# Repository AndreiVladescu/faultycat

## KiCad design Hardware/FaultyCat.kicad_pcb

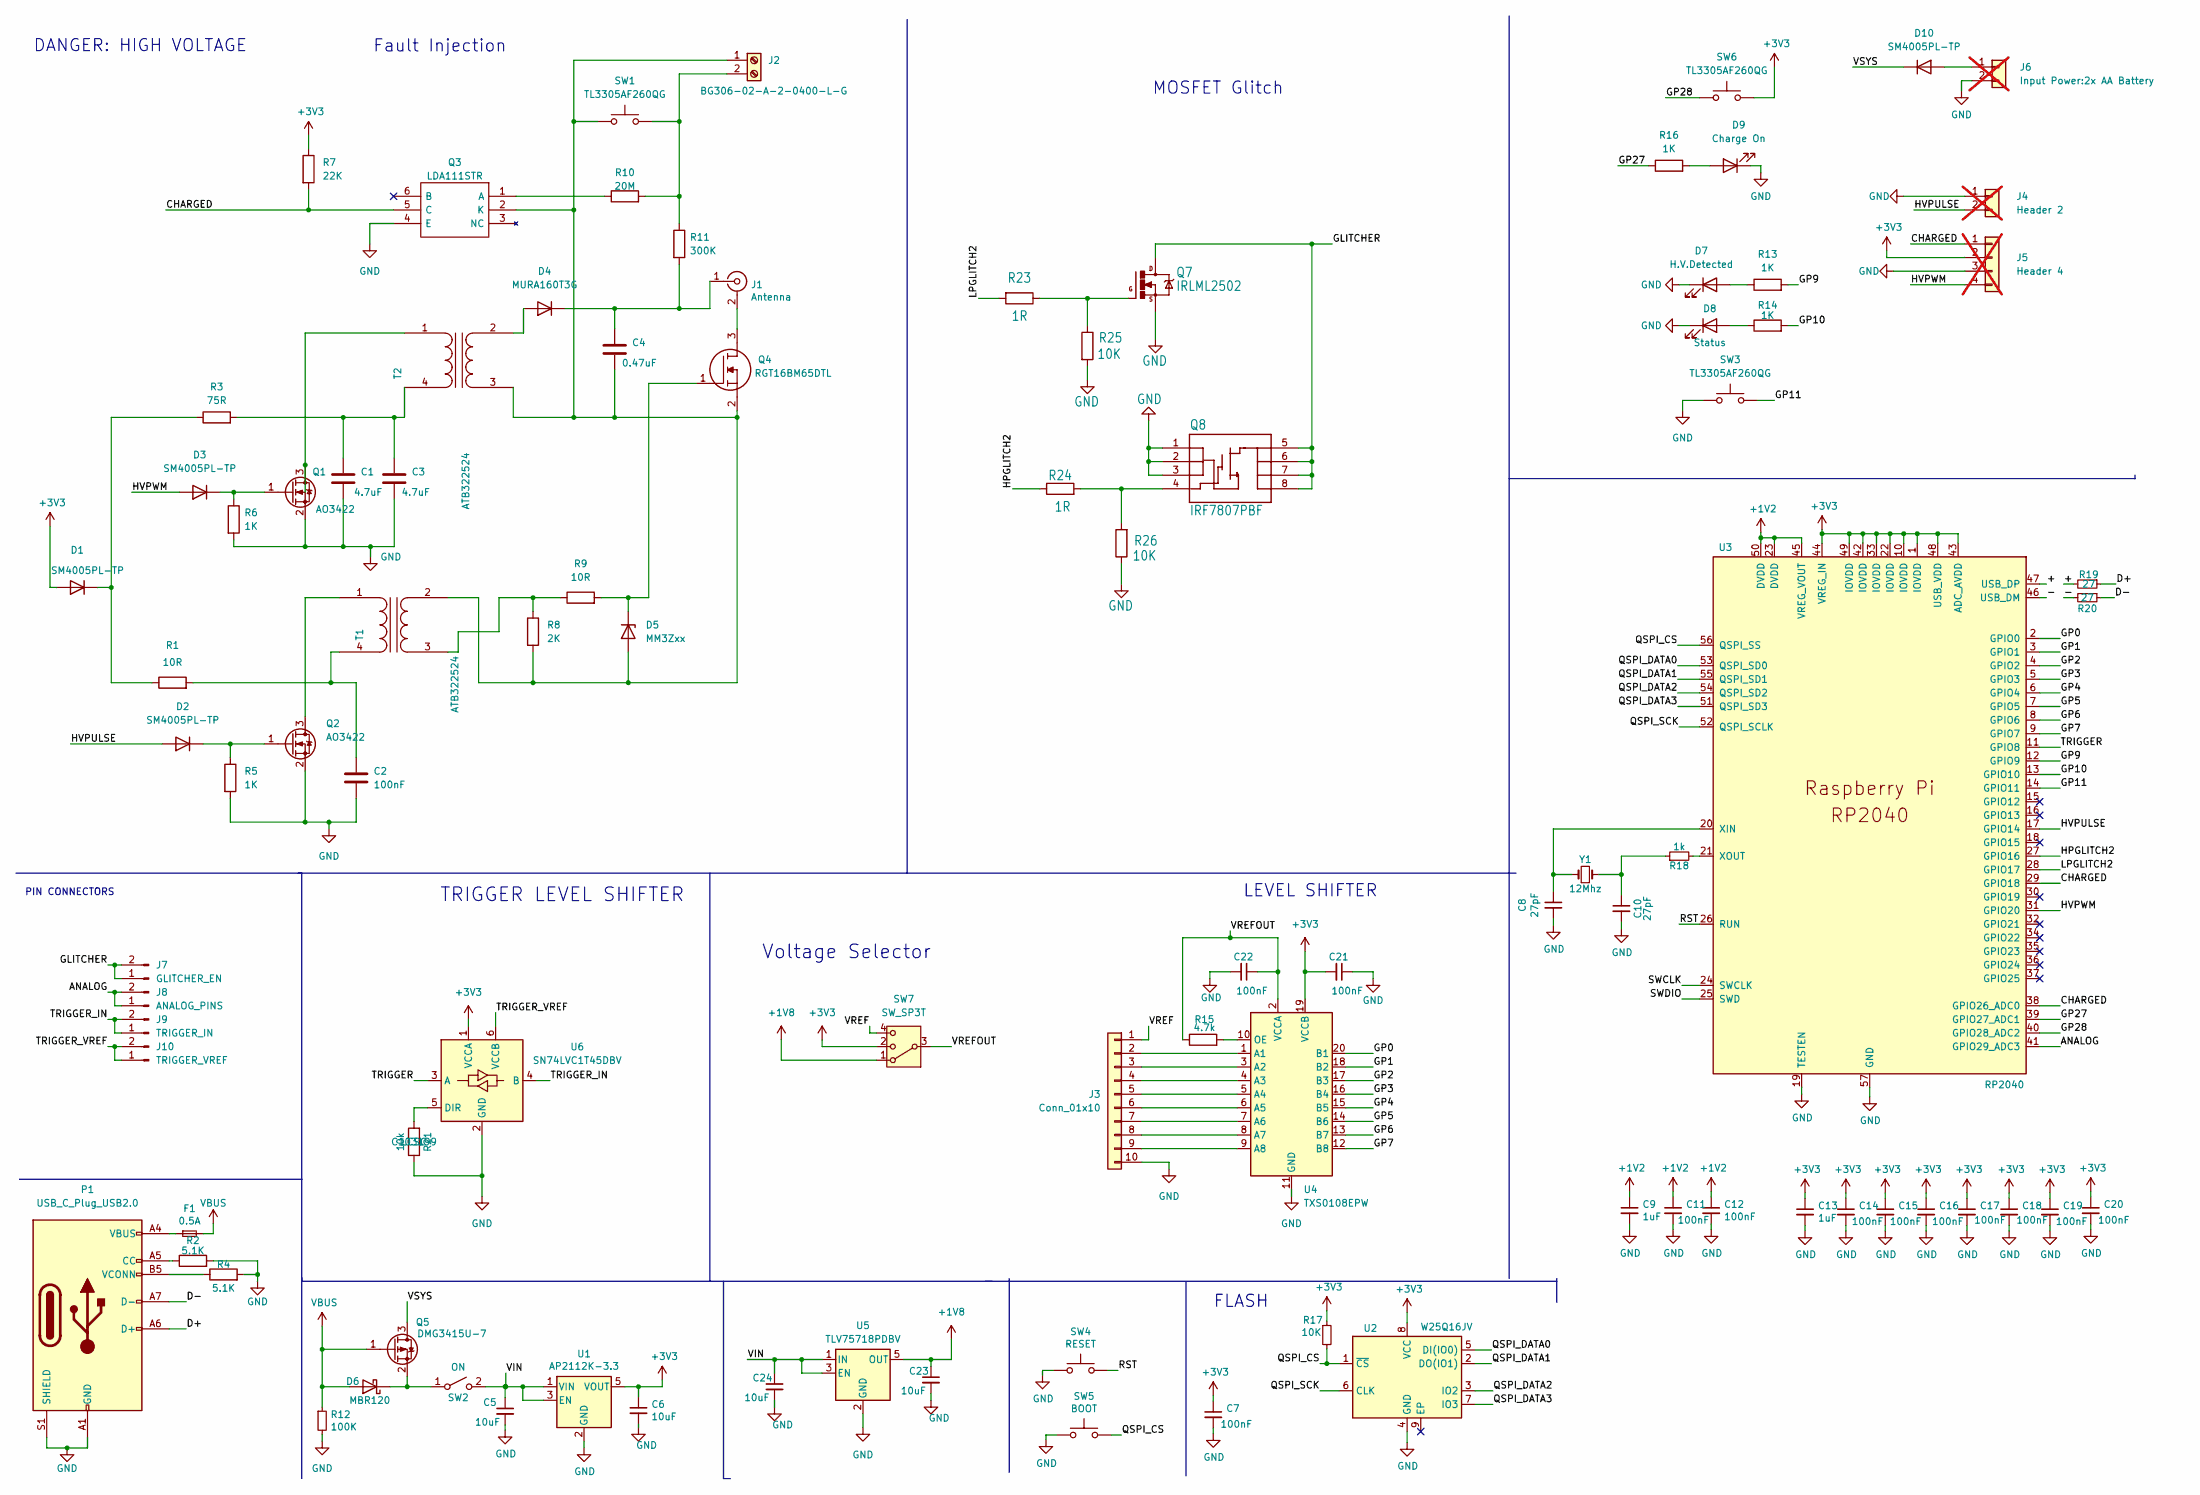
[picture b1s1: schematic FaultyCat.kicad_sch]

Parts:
C1, C3: 4.7uF; C_0805_2012Metric; LCSC# C98192
C2: 100nF; C_0603_1608Metric; LCSC# C30926
C4: 0.47uF; CAPC6153X500N; LCSC# C692326
C5, C6, C23, C24: 10uF; C_0402_1005Metric; LCSC# C15525
C7, C11, C12, C14, C15, C16, C17, C18, C19, C20: 100nF; C_0402_1005Metric; LCSC# C131394
C8, C10: 27pF; C_0603_1608Metric; LCSC# C107045
C9, C13: 1uF; C_0603_1608Metric; LCSC# C26413
C21, C22: 100nF; C_0603_1608Metric; LCSC# C14663
D1, D2, D3, D10: SM4005PL-TP; D_SOD-123F; LCSC# C437593
D4: MURA160T3G; D_SMA; LCSC# C85095
D5: MM3Zxx; D_SOD-323F; LCSC# C263147
D6: MBR120; D_SOD-123; LCSC# C130880
D7: H.V.Detected; LED_0603_1608Metric; LCSC# C157740
D8: Status; LED_0603_1608Metric; LCSC# C192666
D9: Charge On; LED_0603_1608Metric; LCSC# C157740
F1: 0.5A; Fuse_0805_2012Metric; LCSC# C2649565
J1: Antenna; 732511150
J2: BG306-02-A-2-0400-L-G; BG30602A20400LG
J3: Conn_01x10; PinSocket_1x10_P2.54mm_Vertical; LCSC# C5116489
J4: Header 2; PinHeader_1x02_P2.54mm_Vertical; not fitted
J5: Header 4; PinHeader_1x04_P2.54mm_Vertical; not fitted
J6: Input Power:2x AA Battery; PinHeader_1x02_P2.54mm_Vertical; not fitted
J7: GLITCHER_EN; PinSocket_1x02_P2.54mm_Vertical; LCSC# C7499322
J8: ANALOG_PINS; PinSocket_1x02_P2.54mm_Vertical; LCSC# C7499322
J9: TRIGGER_IN; PinSocket_1x02_P2.54mm_Vertical; LCSC# C7499322
J10: TRIGGER_VREF; PinSocket_1x02_P2.54mm_Vertical; LCSC# C7499322
P1: USB_C_Plug_USB2.0; C393939; LCSC# C393939
Q1, Q2: AO3422; SOT-23; LCSC# C37130
Q3: LDA111STR; SOP254P952X470-6N
Q4: RGT16BM65DTL; TO-252-3_TabPin2; LCSC# C3193927
Q5: DMG3415U-7; SOT-23; LCSC# C96616
Q7: IRLML2502; SOT-23; LCSC# C5364308
Q8: IRF7807PBF; SOIC-8_SI; LCSC# C142600
R1, R9: 10R; R_0603_1608Metric; LCSC# C109318
R2, R4: 5.1K; R_0603_1608Metric; LCSC# C23186
R3: 75R; R_0805_2012Metric; LCSC# C141697
R5, R6, R13, R14, R16: 1K; R_0603_1608Metric; LCSC# C22548
R7: 22K; R_0603_1608Metric; LCSC# C114065
R8: 2K; R_0805_2012Metric; LCSC# C114572
R10: 20M; R_2010_5025Metric
R11: 300K; RESC6432X120N
R12: 100K; R_0603_1608Metric; LCSC# C100048
R15: 4.7k; R_0603_1608Metric; LCSC# C116697
R17, R25, R26: 10K; R_0603_1608Metric; LCSC# C103199
R18: 1k; R_0603_1608Metric; LCSC# C115325
R19, R20: 27; R_0603_1608Metric; LCSC# C25224
R21: 10k; R_0603_1608Metric; LCSC# C103199
R23, R24: 1R; R_0603_1608Metric; LCSC# C140111
SW1, SW3, SW6: TL3305AF260QG; TL3305AF160QG; LCSC# C2886902
SW2: ON; OS102011MA1QN1; LCSC# C221829
SW4: RESET; SW_SPST_TL3342; LCSC# C318889
SW5: BOOT; SW_SPST_TL3342; LCSC# C318889
SW7: SW_SP3T; Sw3P1T; LCSC# C361168
T1, T2: ATB322524; ATB3225240110T000; LCSC# C249001
U1: AP2112K-3.3; SOT-23-5; LCSC# C216640
U2: W25Q16JV; W25Q16JVUUIQ
U3: RP2040; RP2040-QFN-56; LCSC# C2040
U4: TXS0108EPW; TSSOP-20_4.4x6.5mm_P0.65mm; LCSC# C1021790
U5: TLV75718PDBV; SOT-23-5; LCSC# C507270
U6: SN74LVC1T45DBV; SOT-23-6; LCSC# C7843
Y1: 12Mhz; Crystal_SMD_5032-2Pin_5.0x3.2mm

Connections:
+1V2: C9.1, C11.1, C12.1, U3.23 (DVDD), U3.45 (VREG_VOUT), U3.50 (DVDD)
+1V8: C23.1, SW7.1, U5.5 (OUT)
+3V3: C6.1, C7.1, C13.1, C14.1, C15.1, C16.1, C17.1, C18.1, C19.1, C20.1, C21.2, D1.2 (A), J5.2, R7.1, R17.1, SW6.2, SW7.2, U1.5 (VOUT), U2.8 (VCC), U3.1 (IOVDD), U3.10 (IOVDD), U3.22 (IOVDD), U3.33 (IOVDD), U3.42 (IOVDD), U3.43 (ADC_AVDD), U3.44 (VREG_IN), U3.48 (USB_VDD), U3.49 (IOVDD), U4.19 (VCCB), U6.1 (VCCA)
/+: R19.2, U3.47 (USB_DP)
/-: R20.2, U3.46 (USB_DM)
/ANALOG: J8.1, J8.2, U3.41 (GPIO29_ADC3)
/CHARGED: J5.1, Q3.5 (C), R7.2, U3.29 (GPIO18), U3.38 (GPIO26_ADC0)
/D+: P1.A6 (D+), R19.1
/D-: P1.A7 (D-), R20.1
/GLITCHER: J7.1, J7.2, Q7.3 (D), Q8.5 (D@4), Q8.6 (D@3), Q8.7 (D@2), Q8.8 (D@1)
/GP0: U3.2 (GPIO0), U4.20 (B1)
/GP1: U3.3 (GPIO1), U4.18 (B2)
/GP2: U3.4 (GPIO2), U4.17 (B3)
/GP3: U3.5 (GPIO3), U4.16 (B4)
/GP4: U3.6 (GPIO4), U4.15 (B5)
/GP5: U3.7 (GPIO5), U4.14 (B6)
/GP6: U3.8 (GPIO6), U4.13 (B7)
/GP7: U3.9 (GPIO7), U4.12 (B8)
/GP9: R13.2, U3.12 (GPIO9)
/GP10: R14.2, U3.13 (GPIO10)
/GP11: SW3.2, U3.14 (GPIO11)
/GP27: R16.1, U3.39 (GPIO27_ADC1)
/GP28: SW6.1, U3.40 (GPIO28_ADC2)
/HPGLITCH2: R24.1, U3.27 (GPIO16)
/HVPULSE: D2.2 (A), J4.2, U3.17 (GPIO14)
/HVPWM: D3.2 (A), J5.4, U3.31 (GPIO20)
/LPGLITCH2: R23.2, U3.28 (GPIO17)
/QSPI_CS: R17.2, SW5.2, U2.1 (~CS), U3.56 (QSPI_SS)
/QSPI_DATA0: U2.5 (DI(IO0)), U3.53 (QSPI_SD0)
/QSPI_DATA1: U2.2 (DO(IO1)), U3.55 (QSPI_SD1)
/QSPI_DATA2: U2.3 (IO2), U3.54 (QSPI_SD2)
/QSPI_DATA3: U2.7 (IO3), U3.51 (QSPI_SD3)
/QSPI_SCK: U2.6 (CLK), U3.52 (QSPI_SCLK)
/RST: SW4.2, U3.26 (RUN)
/SWCLK: U3.24 (SWCLK)
/SWDIO: U3.25 (SWD)
/TRIGGER: U3.11 (GPIO8), U6.3 (A)
/TRIGGER_IN: J9.1, J9.2, U6.4 (B)
/TRIGGER_VREF: J10.1, J10.2, U6.6 (VCCB)
/VIN: C5.1, C24.1, SW2.2 (B), U1.1 (VIN), U1.3 (EN), U5.1 (IN), U5.3 (EN)
/VREF: J3.1, SW7.4
/VREFOUT: C22.1, R15.1, SW7.3, U4.2 (VCCA)
/VSYS: D10.1 (K), Q5.3 (D)
GND: C1.2, C2.2, C3.2, C5.2, C6.2, C7.2, C8.2, C9.2, C10.2, C11.2, C12.2, C13.2, C14.2, C15.2, C16.2, C17.2, C18.2, C19.2, C20.2, C21.1, C22.2, C23.2, C24.2, D7.1 (K), D8.1 (K), D9.1 (K), J3.10, J4.1, J5.3, J6.2, P1.A1 (GND), P1.A12 (GND), P1.B1 (GND), P1.B12 (GND), P1.S1 (SHIELD), Q1.2 (S), Q2.2 (S), Q3.4 (E), Q7.2 (S), Q8.1 (S@1), Q8.2 (S@2), Q8.3 (S@3), R2.2, R4.2, R5.2, R6.2, R12.2, R21.1, R25.2, R26.1, SW3.1, SW4.1, SW5.1, U1.2 (GND), U2.4 (GND), U3.19 (TESTEN), U3.57 (GND), U4.11 (GND), U5.2 (GND), U6.2 (GND)
unnamed: C10.1, R18.1, Y1.2
unnamed: D1.1 (K), R1.1, R3.1
unnamed: D2.1 (K), Q2.1 (G), R5.1
unnamed: D3.1 (K), Q1.1 (G), R6.1
unnamed: D4.2 (A), T2.2 (SA)
unnamed: C4.1, D4.1 (K), J1.1 (In), R11.2
unnamed: C4.2, D5.2 (A), J2.1, Q3.2 (K), Q4.2, R8.2, SW1.1, T1.2 (SA), T2.3 (SB)
unnamed: D5.1 (K), Q4.1, R9.2
unnamed: D6.1 (K), Q5.2 (S), SW2.1 (A)
unnamed: D7.2 (A), R13.1
unnamed: D8.2 (A), R14.1
unnamed: D9.2 (A), R16.2
unnamed: D10.2 (A), J6.1
unnamed: F1.1, P1.A4 (VBUS), P1.A9 (VBUS), P1.B4 (VBUS), P1.B9 (VBUS)
unnamed: J1.2 (Ext), Q4.3
unnamed: J2.2, R10.2, R11.1, SW1.2
unnamed: J3.2, U4.1 (A1)
unnamed: J3.3, U4.3 (A2)
unnamed: J3.4, U4.4 (A3)
unnamed: J3.5, U4.5 (A4)
unnamed: J3.6, U4.6 (A5)
unnamed: J3.7, U4.7 (A6)
unnamed: J3.8, U4.8 (A7)
unnamed: J3.9, U4.9 (A8)
unnamed: P1.A5 (CC), R2.1
unnamed: P1.B5 (VCONN), R4.1
unnamed: Q1.3 (D), T2.1 (AB)
unnamed: Q2.3 (D), T1.1 (AB)
unnamed: Q3.1 (A), R10.1
unnamed: Q7.1 (G), R23.1, R25.1
unnamed: Q8.4 (G), R24.2, R26.2
unnamed: C2.1, R1.2, T1.4 (AA)
unnamed: R8.1, R9.1, T1.3 (SB)
unnamed: C1.1, C3.1, R3.2, T2.4 (AA)
unnamed: C8.1, U3.20 (XIN), Y1.1
unnamed: R18.2, U3.21 (XOUT)
unnamed: R15.2, U4.10 (OE)
unnamed: R21.2, U6.5 (DIR)
VBUS: D6.2 (A), F1.2, Q5.1 (G), R12.1

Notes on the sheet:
Voltage Selector
FLASH
TRIGGER LEVEL SHIFTER
MOSFET Glitch
DANGER: HIGH VOLTAGE
PIN CONNECTORS
LEVEL SHIFTER
Fault Injection

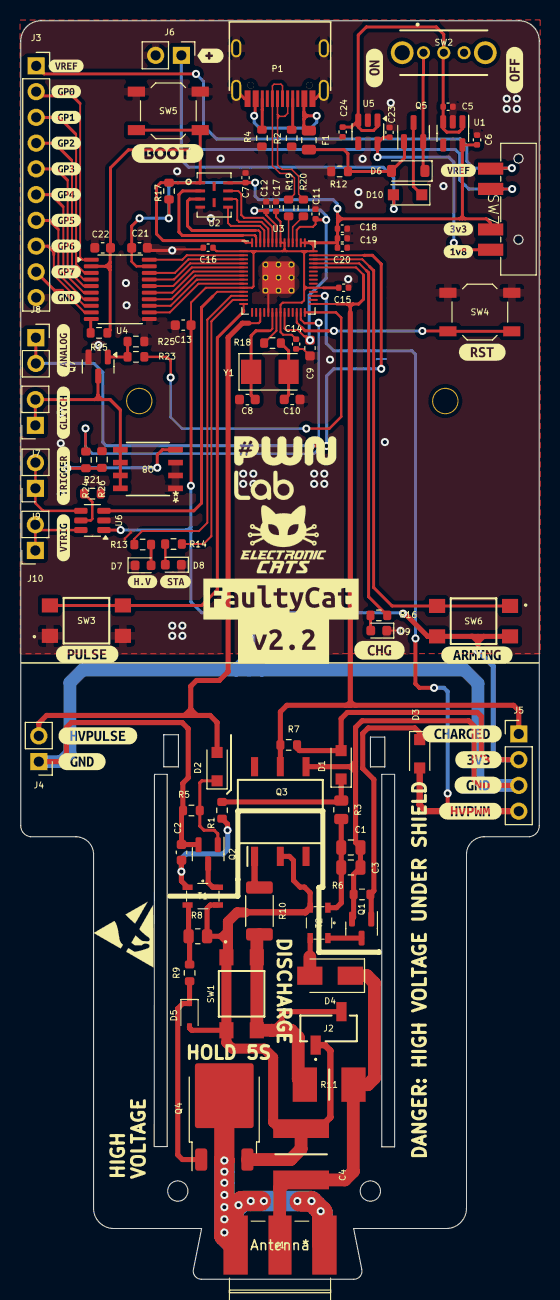
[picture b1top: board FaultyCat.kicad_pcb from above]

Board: 2 copper layers, 51.2 x 124.2 mm, 129 parts (0 on the bottom side), 81 nets.

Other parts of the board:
kibuzzard-67A4D63C: G***; kibuzzard-67A4D63C
kibuzzard-67A4D65E: G***; kibuzzard-67A4D65E
kibuzzard-67A4D80D: G***; kibuzzard-67A4D80D
kibuzzard-67A4D86D: G***; kibuzzard-67A4D86D
kibuzzard-67A4D88F: G***; kibuzzard-67A4D88F
kibuzzard-67A4D93E: G***; kibuzzard-67A4D93E
kibuzzard-67A4D642: G***; kibuzzard-67A4D642
kibuzzard-67A4D648: G***; kibuzzard-67A4D648
kibuzzard-67A4D805: G***; kibuzzard-67A4D805
kibuzzard-67A4D873: G***; kibuzzard-67A4D873
kibuzzard-67A4D879: G***; kibuzzard-67A4D879
kibuzzard-67A4D880: G***; kibuzzard-67A4D880
kibuzzard-67A4D886: G***; kibuzzard-67A4D886
kibuzzard-67A4D896: G***; kibuzzard-67A4D896
kibuzzard-67AA52CA: G***; kibuzzard-67AA52CA
kibuzzard-67AA52D2: G***; kibuzzard-67AA52D2
kibuzzard-69BAD4E7: G***; kibuzzard-69BAD4E7
kibuzzard-642DF5C4: G***; kibuzzard-642DF5C4
kibuzzard-642DF578: G***; kibuzzard-642DF578
kibuzzard-642E0AC9: G***; kibuzzard-642E0AC9
kibuzzard-642E0AD5: G***; kibuzzard-642E0AD5
kibuzzard-642E0AF5: G***; kibuzzard-642E0AF5
kibuzzard-642E0B26: G***; kibuzzard-642E0B26
kibuzzard-642E0B82: G***; kibuzzard-642E0B82
kibuzzard-642E0B91: G***; kibuzzard-642E0B91
kibuzzard-642E11AF: G***; kibuzzard-642E11AF
kibuzzard-642F0B74: G***; kibuzzard-642F0B74
kibuzzard-681E47A0: G***; kibuzzard-681E47A0
kibuzzard-681E47A5: G***; kibuzzard-681E47A5
kibuzzard-681E4798: G***; kibuzzard-681E4798
kibuzzard-6797D18C: G***; kibuzzard-6797D18C
kibuzzard-64767B55: G***; kibuzzard-64767B55
kibuzzard-647546A8: G***; kibuzzard-647546A8
kibuzzard-647546B9: G***; kibuzzard-647546B9
kibuzzard-6475468D: G***; kibuzzard-6475468D

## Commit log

2026-05-12 fix(Hw):C23_And_C24_Added
2026-05-16 Updated project to KiCAD 10
2026-05-16 Excluded calderon & electronic cats logo from BOM
2026-05-17 Fixed shorting resistors for CAN & RS485
2026-05-17 Revert "Fixed shorting resistors for CAN & RS485"
    This reverts commit 6a0c7b165260f2393a2555b54d0e302f1b1791b0.
